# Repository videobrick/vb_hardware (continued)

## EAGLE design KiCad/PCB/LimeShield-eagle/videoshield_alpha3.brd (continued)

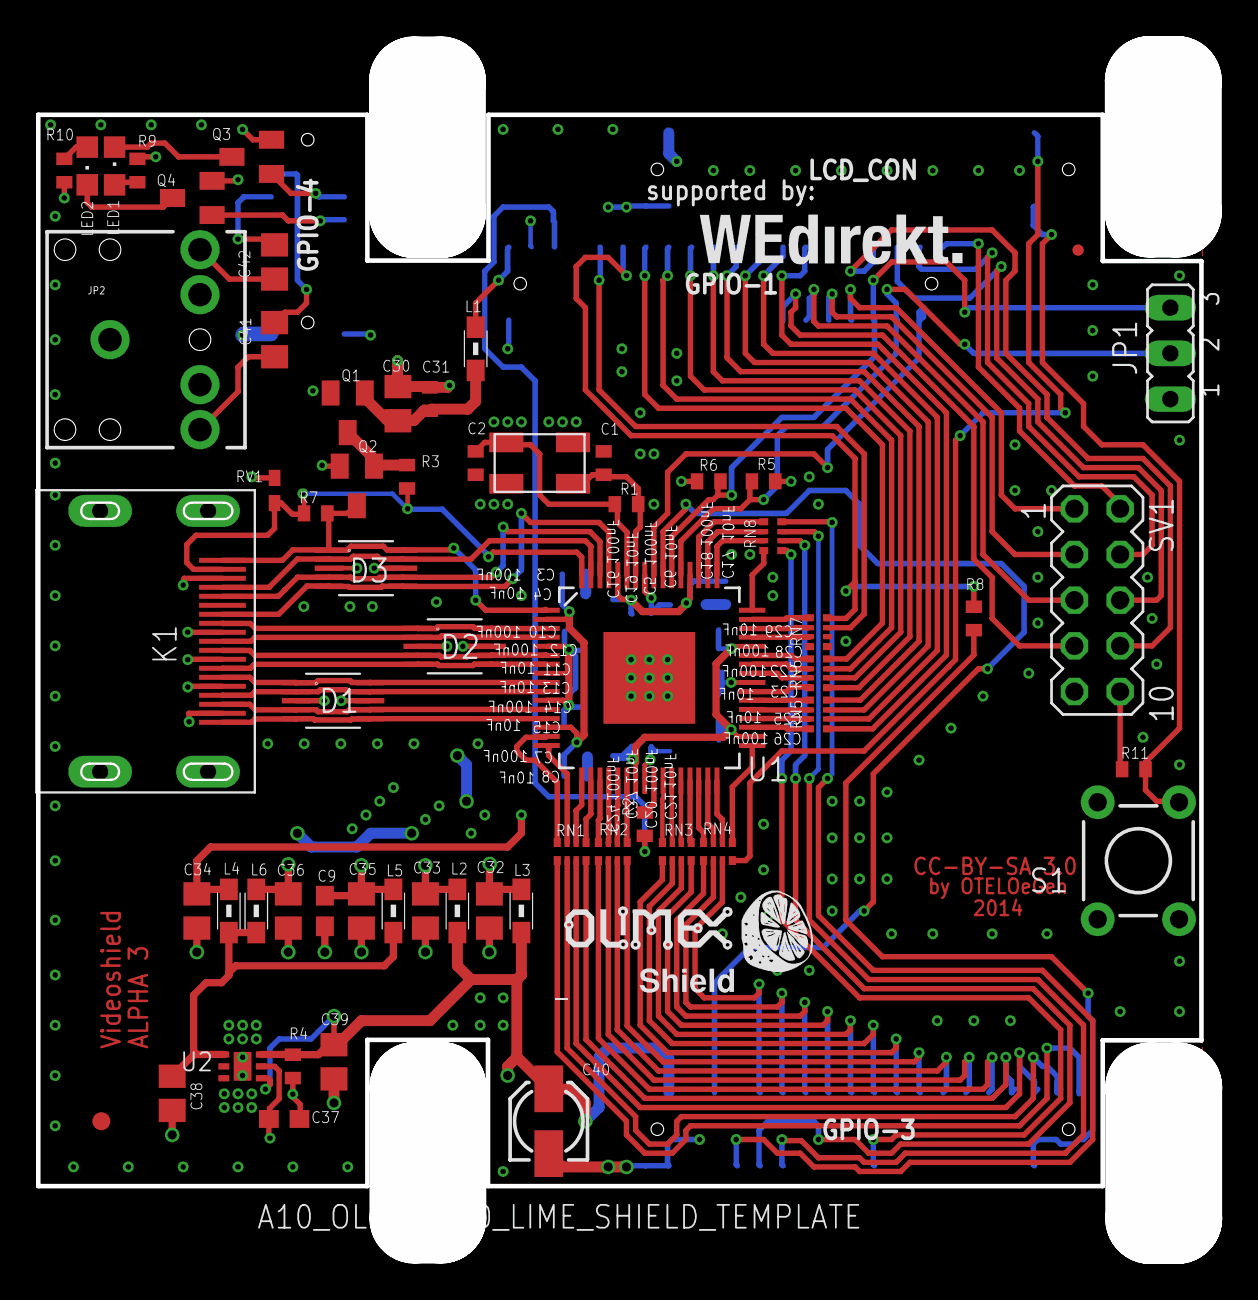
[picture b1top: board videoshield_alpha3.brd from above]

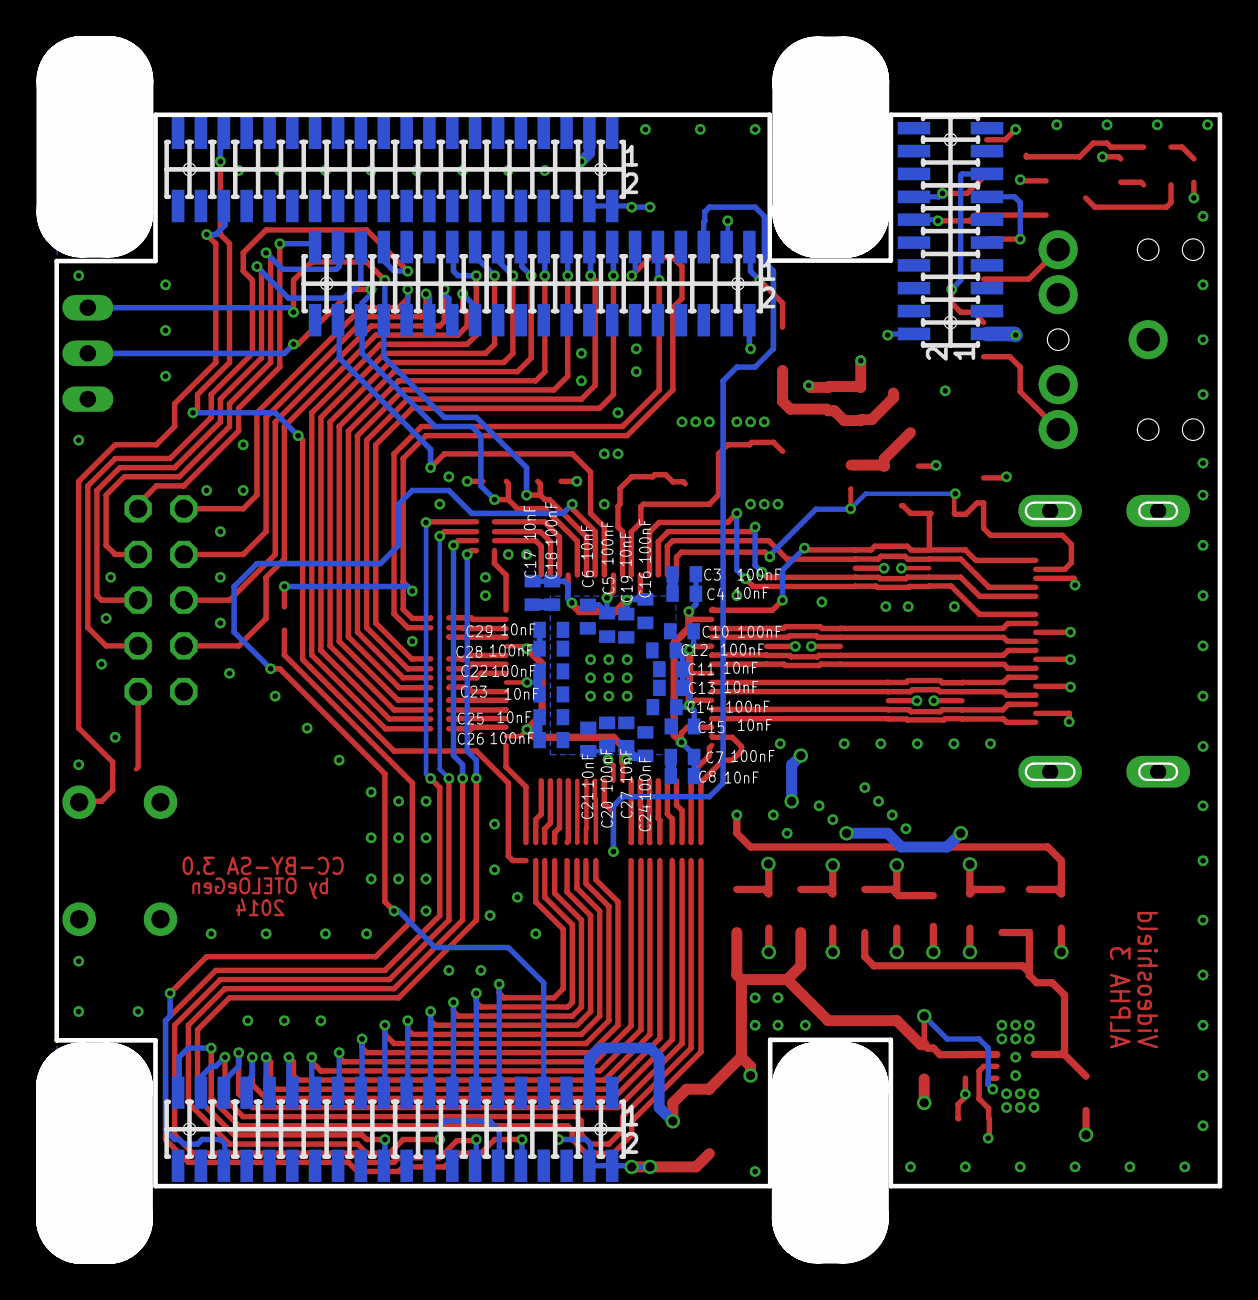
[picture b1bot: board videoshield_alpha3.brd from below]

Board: 8 copper layers, 64.6 x 63.2 mm, 91 parts (26 on the bottom side), 114 nets.

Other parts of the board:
U$1: WEDIREKT
U$2: OLIMEXLIME

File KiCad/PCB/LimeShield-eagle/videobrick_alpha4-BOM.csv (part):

"Part";"Value";"Device";"Package";"Description";"MF";"MPN";"OC_FARNELL";"OC_NEWARK";"PACKAGE";"SUPPLIER";"TP_SIGNAL_NAME";
"C1";"47pF";"C-EUC0402";"C0402";"CAPACITOR, European symbol";"";"";"";"";"";"";"";
"C2";"47pF";"C-EUC0402";"C0402";"CAPACITOR, European symbol";"";"";"";"";"";"";"";
"C3";"100nF";"C-EUC0402";"C0402";"CAPACITOR, European symbol";"";"";"";"";"";"";"";
"C4";"10nF";"C-EUC0402";"C0402";"CAPACITOR, European symbol";"";"";"";"";"";"";"";
"C5";"100nF";"C-EUC0402";"C0402";"CAPACITOR, European symbol";"";"";"";"";"";"";"";
"C6";"10nF";"C-EUC0402";"C0402";"CAPACITOR, European symbol";"";"";"";"";"";"";"";
"C7";"100nF";"C-EUC0402";"C0402";"CAPACITOR, European symbol";"";"";"";"";"";"";"";
"C8";"10nF";"C-EUC0402";"C0402";"CAPACITOR, European symbol";"";"";"";"";"";"";"";
"C9";"1uF";"C-EUC0603";"C0603";"CAPACITOR, European symbol";"";"";"";"";"";"";"";
"C10";"100nF";"C-EUC0402";"C0402";"CAPACITOR, European symbol";"";"";"";"";"";"";"";
"C11";"10nF";"C-EUC0402";"C0402";"CAPACITOR, European symbol";"";"";"";"";"";"";"";
"C12";"100nF";"C-EUC0402";"C0402";"CAPACITOR, European symbol";"";"";"";"";"";"";"";
"C13";"10nF";"C-EUC0402";"C0402";"CAPACITOR, European symbol";"";"";"";"";"";"";"";
"C14";"100nF";"C-EUC0402";"C0402";"CAPACITOR, European symbol";"";"";"";"";"";"";"";
"C15";"10nF";"C-EUC0402";"C0402";"CAPACITOR, European symbol";"";"";"";"";"";"";"";
"C16";"100nF";"C-EUC0402";"C0402";"CAPACITOR, European symbol";"";"";"";"";"";"";"";
"C17";"10nF";"C-EUC0402";"C0402";"CAPACITOR, European symbol";"";"";"";"";"";"";"";
"C18";"100nF";"C-EUC0402";"C0402";"CAPACITOR, European symbol";"";"";"";"";"";"";"";
"C19";"10nF";"C-EUC0402";"C0402";"CAPACITOR, European symbol";"";"";"";"";"";"";"";
"C20";"100nF";"C-EUC0402";"C0402";"CAPACITOR, European symbol";"";"";"";"";"";"";"";
"C21";"10nF";"C-EUC0402";"C0402";"CAPACITOR, European symbol";"";"";"";"";"";"";"";
"C22";"100nF";"C-EUC0402";"C0402";"CAPACITOR, European symbol";"";"";"";"";"";"";"";
"C23";"10nF";"C-EUC0402";"C0402";"CAPACITOR, European symbol";"";"";"";"";"";"";"";
"C24";"100nF";"C-EUC0402";"C0402";"CAPACITOR, European symbol";"";"";"";"";"";"";"";
"C25";"10nF";"C-EUC0402";"C0402";"CAPACITOR, European symbol";"";"";"";"";"";"";"";
"C26";"100nF";"C-EUC0402";"C0402";"CAPACITOR, European symbol";"";"";"";"";"";"";"";
"C27";"10nF";"C-EUC0402";"C0402";"CAPACITOR, European symbol";"";"";"";"";"";"";"";
"C28";"100nF";"C-EUC0402";"C0402";"CAPACITOR, European symbol";"";"";"";"";"";"";"";
"C29";"10nF";"C-EUC0402";"C0402";"CAPACITOR, European symbol";"";"";"";"";"";"";"";
"C30";"10uF";"C-EUC0805";"C0805";"CAPACITOR, European symbol";"";"";"";"";"";"";"";
"C31";"10nF";"C-EUC0402";"C0402";"CAPACITOR, European symbol";"";"";"";"";"";"";"";
"C32";"10uF";"C-EUC0805";"C0805";"CAPACITOR, European symbol";"";"";"";"";"";"";"";
"C33";"10uF";"C-EUC0805";"C0805";"CAPACITOR, European symbol";"";"";"";"";"";"";"";
"C34";"10uF";"C-EUC0805";"C0805";"CAPACITOR, European symbol";"";"";"";"";"";"";"";
"C35";"10uF";"C-EUC0805";"C0805";"CAPACITOR, European symbol";"";"";"";"";"";"";"";
"C36";"10uF";"C-EUC0805";"C0805";"CAPACITOR, European symbol";"";"";"";"";"";"";"";
"C37";"1uF";"C-EUC0603";"C0603";"CAPACITOR, European symbol";"";"";"";"";"";"";"";
"C38";"10uF";"C-EUC0805";"C0805";"CAPACITOR, European symbol";"";"";"";"";"";"";"";
"C39";"10uF";"C-EUC0805";"C0805";"CAPACITOR, European symbol";"";"";"";"";"";"";"";
"C40";"100uF";"CPOL-EU153CLV-0405";"153CLV-0405";"POLARIZED CAPACITOR, European symbol";"";"";"";"";"";"";"";
"C41";"10uF";"C-EUC0805";"C0805";"CAPACITOR, European symbol";"";"";"";"";"";"";"";
"C42";"10uF";"C-EUC0805";"C0805";"CAPACITOR, European symbol";"";"";"";"";"";"";"";
"CON1";"A10_OLINUXINO_LIME_SHIELD_TEMPLATE";"A10_OLINUXINO_LIME_SHIELD_TEMPLATE";"A10_OLINUXINO_LIME_SHIELD";"";"";"";"";"";"";"";"";
"D1";"";"WE-TVS_82401444";"WE-TVS_MSOP-10L";"TVS Diode Array WE-TVS, Super Speed Serie";"";"82401444";"1825863";"79R6952";"MSOP-10L";"Wuerth Elektronik";"";
"D2";"";"WE-TVS_82401444";"WE-TVS_MSOP-10L";"TVS Diode Array WE-TVS, Super Speed Serie";"";"82401444";"1825863";"79R6952";"MSOP-10L";"Wuerth Elektronik";"";
"D3";"";"WE-TVS_82401444";"WE-TVS_MSOP-10L";"TVS Diode Array WE-TVS, Super Speed Serie";"";"82401444";"1825863";"79R6952";"MSOP-10L";"Wuerth Elektronik";"";
"FID1";"FIDUCIALUFIDUCIAL";"FIDUCIALUFIDUCIAL";"MICRO-FIDUCIAL";"Fiducial Alignment Points";"";"";"";"";"";"";"";
"FID2";"FIDUCIAL1X2";"FIDUCIAL1X2";"FIDUCIAL-1X2";"Fiducial Alignment Points";"";"";"";"";"";"";"";
"JP1";"";"JP2E";"JP2";"JUMPER";"";"";"";"";"";"";"";
"JP2";"";"AUDIO-JACKPTH";"AUDIO-JACK";"3.5mm Audio Jack";"";"";"";"";"";"";"";
"K1";"685119134923";"685119134923";"685119134923";"WR-COM SMT Horizontal HDMI, 19 pins";"";"";"";"";"";"";"";
"L1";"";"WE-CBF-742792040_0805";"0805";"SMD EMI Suppression Ferrite Beads WE-CBF";"";"742792040";"1635735";"08P2371";"IND-0805";"Wuerth Elektronik";"";
"L2";"";"WE-CBF-742792040_0805";"0805";"SMD EMI Suppression Ferrite Beads WE-CBF";"";"742792040";"1635735";"08P2371";"IND-0805";"Wuerth Elektronik";"";
"L3";"";"WE-CBF-742792040_0805";"0805";"SMD EMI Suppression Ferrite Beads WE-CBF";"";"742792040";"1635735";"08P2371";"IND-0805";"Wuerth Elektronik";"";
"L4";"";"WE-CBF-742792040_0805";"0805";"SMD EMI Suppression Ferrite Beads WE-CBF";"";"742792040";"1635735";"08P2371";"IND-0805";"Wuerth Elektronik";"";
"L5";"";"WE-CBF-742792040_0805";"0805";"SMD EMI Suppression Ferrite Beads WE-CBF";"";"742792040";"1635735";"08P2371";"IND-0805";"Wuerth Elektronik";"";
"L6";"";"WE-CBF-742792040_0805";"0805";"SMD EMI Suppression Ferrite Beads WE-CBF";"";"742792040";"1635735";"08P2371";"IND-0805";"Wuerth Elektronik";"";
"LED1";"";"LEDCHIPLED_0805";"CHIPLED_0805";"LED";"";"";"";"";"";"";"";
"LED2";"";"LEDCHIPLED_0805";"CHIPLED_0805";"LED";"";"";"";"";"";"";"";
"LOGO1";"OSHW-LOGOL";"OSHW-LOGOL";"OSHW-LOGO-L";"Open Source Hardware Logo This logo indicates the piece of hardware it is found on incorporates a OSHW license and/or adheres to the definition of open source hardware found here: http://freedomdefined.org/OSHW";"";"";"";"";"";"";"";
"Q1";"BSS123";"BSS123";"SOT23";"N-CHANNEL MOS FET";"";"";"";"";"";"";"";
"Q2";"BSS123";"BSS123";"SOT23";"N-CHANNEL MOS FET";"";"";"";"";"";"";"";
"Q3";"BSS123";"BSS123";"SOT23";"N-CHANNEL MOS FET";"";"";"";"";"";"";"";
"Q4";"BSS123";"BSS123";"SOT23";"N-CHANNEL MOS FET";"";"";"";"";"";"";"";
"R1";"390R";"R-EU_R0402";"R0402";"RESISTOR, European symbol";"";"";"";"";"";"";"";
"R2";"33R";"R-EU_R0402";"R0402";"RESISTOR, European symbol";"";"";"";"";"";"";"";
"R3";"100k";"R-EU_R0402";"R0402";"RESISTOR, European symbol";"";"";"";"";"";"";"";
"R4";"100k";"R-EU_R0402";"R0402";"RESISTOR, European symbol";"";"";"";"";"";"";"";
"R5";"4k7";"R-EU_R0402";"R0402";"RESISTOR, European symbol";"";"";"";"";"";"";"";
"R6";"4k7";"R-EU_R0402";"R0402";"RESISTOR, European symbol";"";"";"";"";"";"";"";
"R7";"1k";"R-EU_R0402";"R0402";"RESISTOR, European symbol";"";"";"";"";"";"";"";
"R8";"0R";"R-EU_R0402";"R0402";"RESISTOR, European symbol";"";"";"";"";"";"";"";
"R9";"330R";"R-EU_R0402";"R0402";"RESISTOR, European symbol";"";"";"";"";"";"";"";
"R10";"330R";"R-EU_R0402";"R0402";"RESISTOR, European symbol";"";"";"";"";"";"";"";
"R11";"4k7";"R-EU_R0402";"R0402";"RESISTOR, European symbol";"";"";"";"";"";"";"";
"RN1";"33R";"4R-N0402ARV341";"4X0402ARV341";"Array Chip Resistor";"";"";"unknown";"unknown";"";"";"";
"RN2";"33R";"4R-N0402ARV341";"4X0402ARV341";"Array Chip Resistor";"";"";"unknown";"unknown";"";"";"";
"RN3";"33R";"4R-N0402ARV341";"4X0402ARV341";"Array Chip Resistor";"";"";"unknown";"unknown";"";"";"";
"RN4";"33R";"4R-N0402ARV341";"4X0402ARV341";"Array Chip Resistor";"";"";"unknown";"unknown";"";"";"";
"RN5";"33R";"4R-N0402ARV341";"4X0402ARV341";"Array Chip Resistor";"";"";"unknown";"unknown";"";"";"";
"RN6";"33R";"4R-N0402ARV341";"4X0402ARV341";"Array Chip Resistor";"";"";"unknown";"unknown";"";"";"";
"RN7";"33R";"4R-N0402ARV341";"4X0402ARV341";"Array Chip Resistor";"";"";"unknown";"unknown";"";"";"";
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
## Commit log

2014-09-18 added Alpha3 of LimeShield PCB
2014-09-24 version die bestellt wird
2014-10-16 added overview diagramm
2015-02-06 added KiCad-Design
